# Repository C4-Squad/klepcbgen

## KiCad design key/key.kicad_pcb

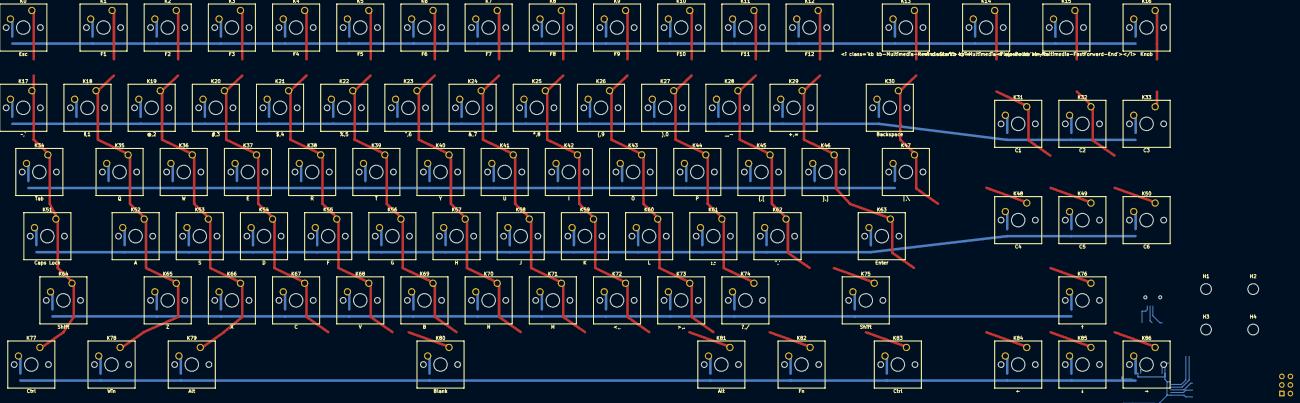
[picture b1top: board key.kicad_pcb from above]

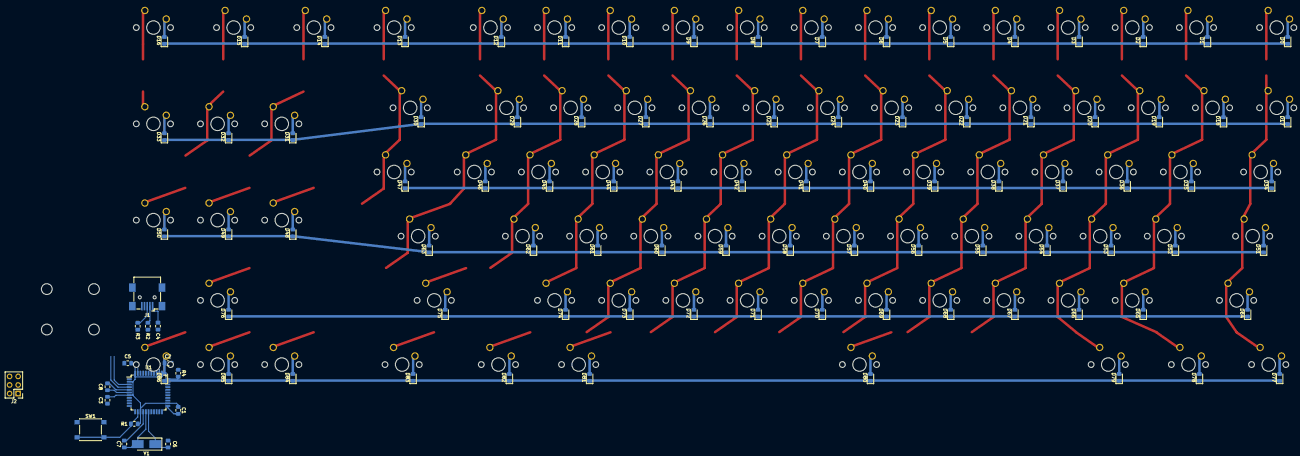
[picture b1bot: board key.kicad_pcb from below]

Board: 2 copper layers, 195 parts (104 on the bottom side), 121 nets.

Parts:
C1, C2, C3, C4: 0.1u; C_0805_2012Metric_Pad1.15x1.40mm_HandSolder
C5: 4.7u; C_0805_2012Metric_Pad1.15x1.40mm_HandSolder
C6, C7: 22p; C_0805_2012Metric_Pad1.15x1.40mm_HandSolder
C8: 1u; C_0805_2012Metric_Pad1.15x1.40mm_HandSolder
D0, D1, D2, D3, D4, D5, D6, D7, D8, D9, D10, D11, D12, D13, D14, D15, D16, D17, D18, D19, D20, D21, D22, D23, D24, D25, D26, D27, D28, D29, D30, D31, D32, D33, D34, D35, D36, D37, D38, D39, D40, D41, D42, D43, D44, D45, D46, D47, D48, D49, D50, D51, D52, D53, D54, D55, D56, D57, D58, D59, D60, D61, D62, D63, D64, D65, D66, D67, D68, D69, D70, D71, D72, D73, D74, D75, D76, D77, D78, D79, D80, D81, D82, D83, D84, D85, D86: D; D_0805_2012Metric_Pad1.15x1.40mm_HandSolder
H1, H2, H3, H4: MountingHole; MountingHole_3.2mm_M3_DIN965
J1: USB_mini_micro_B; USB_Mini-B_Wuerth_65100516121_Horizontal
J2: Conn_02x03_Odd_Even; PinHeader_2x03_P2.54mm_Vertical
K0: Esc; SW_Cherry_MX_1.00u_PCB
K1: F1; SW_Cherry_MX_1.00u_PCB
K2: F2; SW_Cherry_MX_1.00u_PCB
K3: F3; SW_Cherry_MX_1.00u_PCB
K4: F4; SW_Cherry_MX_1.00u_PCB
K5: F5; SW_Cherry_MX_1.00u_PCB
K6: F6; SW_Cherry_MX_1.00u_PCB
K7: F7; SW_Cherry_MX_1.00u_PCB
K8: F8; SW_Cherry_MX_1.00u_PCB
K9: F9; SW_Cherry_MX_1.00u_PCB
K10: F10; SW_Cherry_MX_1.00u_PCB
K11: F11; SW_Cherry_MX_1.00u_PCB
K12: F12; SW_Cherry_MX_1.00u_PCB
K13: <i class='kb kb-Multimedia-Rewind-Start'></i>; SW_Cherry_MX_1.00u_PCB
K14: <i class='kb kb-Multimedia-Play-Pause'></i>; SW_Cherry_MX_1.00u_PCB
K15: <i class='kb kb-Multimedia-FastForward-End'></i>; SW_Cherry_MX_1.00u_PCB
K16: Knob; SW_Cherry_MX_1.00u_PCB
K17: ~~,`; SW_Cherry_MX_1.00u_PCB
K18: !,1; SW_Cherry_MX_1.00u_PCB
K19: @,2; SW_Cherry_MX_1.00u_PCB
K20: #,3; SW_Cherry_MX_1.00u_PCB
K21: $,4; SW_Cherry_MX_1.00u_PCB
K22: %,5; SW_Cherry_MX_1.00u_PCB
K23: ^,6; SW_Cherry_MX_1.00u_PCB
K24: &,7; SW_Cherry_MX_1.00u_PCB
K25: *,8; SW_Cherry_MX_1.00u_PCB
K26: (,9; SW_Cherry_MX_1.00u_PCB
K27: ),0; SW_Cherry_MX_1.00u_PCB
K28: _,-; SW_Cherry_MX_1.00u_PCB
K29: +,=; SW_Cherry_MX_1.00u_PCB
K30: Backspace; SW_Cherry_MX_2.00u_PCB
K31: C1; SW_Cherry_MX_1.00u_PCB
K32: C2; SW_Cherry_MX_1.00u_PCB
K33: C3; SW_Cherry_MX_1.00u_PCB
K34: Tab; SW_Cherry_MX_1.50u_PCB
K35: Q; SW_Cherry_MX_1.00u_PCB
K36: W; SW_Cherry_MX_1.00u_PCB
K37: E; SW_Cherry_MX_1.00u_PCB
K38: R; SW_Cherry_MX_1.00u_PCB
K39: T; SW_Cherry_MX_1.00u_PCB
K40: Y; SW_Cherry_MX_1.00u_PCB
K41: U; SW_Cherry_MX_1.00u_PCB
K42: I; SW_Cherry_MX_1.00u_PCB
K43: O; SW_Cherry_MX_1.00u_PCB
K44: P; SW_Cherry_MX_1.00u_PCB
K45: {,[; SW_Cherry_MX_1.00u_PCB
K46: },]; SW_Cherry_MX_1.00u_PCB
K47: |,\; SW_Cherry_MX_1.50u_PCB
K48: C4; SW_Cherry_MX_1.00u_PCB
K49: C5; SW_Cherry_MX_1.00u_PCB
K50: C6; SW_Cherry_MX_1.00u_PCB
K51: Caps Lock; SW_Cherry_MX_1.75u_PCB
K52: A; SW_Cherry_MX_1.00u_PCB
K53: S; SW_Cherry_MX_1.00u_PCB
K54: D; SW_Cherry_MX_1.00u_PCB
K55: F; SW_Cherry_MX_1.00u_PCB
K56: G; SW_Cherry_MX_1.00u_PCB
K57: H; SW_Cherry_MX_1.00u_PCB
K58: J; SW_Cherry_MX_1.00u_PCB
K59: K; SW_Cherry_MX_1.00u_PCB
K60: L; SW_Cherry_MX_1.00u_PCB
K61: :,;; SW_Cherry_MX_1.00u_PCB
K62: ",'; SW_Cherry_MX_1.00u_PCB
K63: Enter; SW_Cherry_MX_2.25u_PCB
K64: Shift; SW_Cherry_MX_2.25u_PCB
K65: Z; SW_Cherry_MX_1.00u_PCB
K66: X; SW_Cherry_MX_1.00u_PCB
K67: C; SW_Cherry_MX_1.00u_PCB
K68: V; SW_Cherry_MX_1.00u_PCB
K69: B; SW_Cherry_MX_1.00u_PCB
K70: N; SW_Cherry_MX_1.00u_PCB
K71: M; SW_Cherry_MX_1.00u_PCB
K72: <,,; SW_Cherry_MX_1.00u_PCB
K73: >,.; SW_Cherry_MX_1.00u_PCB
K74: ?,/; SW_Cherry_MX_1.00u_PCB
K75: Shift; SW_Cherry_MX_2.75u_PCB
K76: ↑; SW_Cherry_MX_1.00u_PCB
K77: Ctrl; SW_Cherry_MX_1.25u_PCB
K78: Win; SW_Cherry_MX_1.25u_PCB
K79, K81: Alt; SW_Cherry_MX_1.25u_PCB
K80: Blank; SW_Cherry_MX_6.25u_PCB
K82: Fn; SW_Cherry_MX_1.25u_PCB
K83: Ctrl; SW_Cherry_MX_1.75u_PCB
K84: ←; SW_Cherry_MX_1.00u_PCB
K85: ↓; SW_Cherry_MX_1.00u_PCB
K86: →; SW_Cherry_MX_1.00u_PCB
R1, R4: 10k; R_0805_2012Metric_Pad1.15x1.40mm_HandSolder
R2, R3: 22R; R_0805_2012Metric_Pad1.15x1.40mm_HandSolder
SW1: SW_Push; SW_Push_1P1T_NO_6x6mm_H9.5mm
U1: ATmega32U4-AU; TQFP-44_10x10mm_P0.8mm
Y1: Crystal; Crystal_SMD_5032-2Pin_5.0x3.2mm_HandSoldering

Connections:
/Col_0: K0.1, K17.1, K34.1, K51.1, K64.1, K77.1, U1.32
/Col_1: K1.1, K18.1, K35.1, K52.1, K65.1, K78.1, U1.31
/Col_2: K2.1, K19.1, K36.1, K53.1, K66.1, K79.1, U1.30
/Col_3: K3.1, K20.1, K37.1, K54.1, K67.1, K80.1, U1.29
/Col_4: K4.1, K21.1, K38.1, K55.1, K68.1, K81.1, U1.28
/Col_5: K5.1, K22.1, K39.1, K56.1, K69.1, K82.1, U1.27
/Col_6: K6.1, K23.1, K40.1, K57.1, K70.1, K83.1, U1.26
/Col_7: K7.1, K24.1, K41.1, K58.1, K71.1, K84.1, U1.25
/Col_8: K8.1, K25.1, K42.1, K59.1, K72.1, K85.1, U1.36
/Col_9: K9.1, K26.1, K43.1, K60.1, K73.1, K86.1, U1.37
/Col_10: K10.1, K27.1, K44.1, K61.1, K74.1, U1.38
/Col_11: K11.1, K28.1, K45.1, K62.1, K75.1, U1.39
/Col_12: K12.1, K29.1, K46.1, K63.1, K76.1, U1.40
/Col_13: K13.1, K30.1, K47.1, K48.1, U1.41
/Col_14: K14.1, K31.1, K49.1, U1.22
/Col_15: K15.1, K32.1, K50.1, U1.19
/Col_16: K16.1, K33.1, U1.20
/Row_0: D0.1, D1.1, D2.1, D3.1, D4.1, D5.1, D6.1, D7.1, D8.1, D9.1, D10.1, D11.1, D12.1, D13.1, D14.1, D15.1, D16.1, U1.18
/Row_1: D17.1, D18.1, D19.1, D20.1, D21.1, D22.1, D23.1, D24.1, D25.1, D26.1, D27.1, D28.1, D29.1, D30.1, D31.1, D32.1, D33.1, U1.12
/Row_2: D34.1, D35.1, D36.1, D37.1, D38.1, D39.1, D40.1, D41.1, D42.1, D43.1, D44.1, D45.1, D46.1, D47.1, J2.2, U1.11
/Row_3: D48.1, D49.1, D50.1, D51.1, D52.1, D53.1, D54.1, D55.1, D56.1, D57.1, D58.1, D59.1, D60.1, D61.1, D62.1, D63.1, J2.4, U1.10
/Row_4: D64.1, D65.1, D66.1, D67.1, D68.1, D69.1, D70.1, D71.1, D72.1, D73.1, D74.1, D75.1, D76.1, J2.3, U1.9
/Row_5: D77.1, D78.1, D79.1, D80.1, D81.1, D82.1, D83.1, D84.1, D85.1, D86.1, U1.8
GND: C1.2, C2.2, C3.2, C4.2, C5.2, C6.2, C7.2, C8.2, J1.5, J1.6, J2.5, R4.1, SW1.1, U1.5, U1.15, U1.23, U1.35, U1.43
unnamed: C6.1, U1.17, Y1.1
unnamed: C7.1, U1.16, Y1.2
unnamed: C8.1, U1.6
unnamed: D0.2, K0.2
unnamed: D1.2, K1.2
unnamed: D2.2, K2.2
unnamed: D3.2, K3.2
unnamed: D4.2, K4.2
unnamed: D5.2, K5.2
unnamed: D6.2, K6.2
unnamed: D7.2, K7.2
unnamed: D8.2, K8.2
unnamed: D9.2, K9.2
unnamed: D10.2, K10.2
unnamed: D11.2, K11.2
unnamed: D12.2, K12.2
unnamed: D13.2, K13.2
unnamed: D14.2, K14.2
unnamed: D15.2, K15.2
unnamed: D16.2, K16.2
unnamed: D17.2, K17.2
unnamed: D18.2, K18.2
unnamed: D19.2, K19.2
unnamed: D20.2, K20.2
unnamed: D21.2, K21.2
unnamed: D22.2, K22.2
unnamed: D23.2, K23.2
unnamed: D24.2, K24.2
unnamed: D25.2, K25.2
unnamed: D26.2, K26.2
unnamed: D27.2, K27.2
unnamed: D28.2, K28.2
unnamed: D29.2, K29.2
unnamed: D30.2, K30.2
unnamed: D31.2, K31.2
unnamed: D32.2, K32.2
unnamed: D33.2, K33.2
unnamed: D34.2, K34.2
unnamed: D35.2, K35.2
unnamed: D36.2, K36.2
unnamed: D37.2, K37.2
unnamed: D38.2, K38.2
unnamed: D39.2, K39.2
unnamed: D40.2, K40.2
unnamed: D41.2, K41.2
unnamed: D42.2, K42.2
unnamed: D43.2, K43.2
unnamed: D44.2, K44.2
unnamed: D45.2, K45.2
unnamed: D46.2, K46.2
unnamed: D47.2, K47.2
unnamed: D48.2, K48.2
unnamed: D49.2, K49.2
unnamed: D50.2, K50.2
unnamed: D51.2, K51.2
unnamed: D52.2, K52.2
unnamed: D53.2, K53.2
unnamed: D54.2, K54.2
unnamed: D55.2, K55.2
unnamed: D56.2, K56.2
unnamed: D57.2, K57.2
unnamed: D58.2, K58.2
unnamed: D59.2, K59.2
unnamed: D60.2, K60.2
unnamed: D61.2, K61.2
unnamed: D62.2, K62.2
unnamed: D63.2, K63.2
unnamed: D64.2, K64.2
unnamed: D65.2, K65.2
unnamed: D66.2, K66.2
unnamed: D67.2, K67.2
unnamed: D68.2, K68.2
unnamed: D69.2, K69.2
unnamed: D70.2, K70.2
unnamed: D71.2, K71.2
unnamed: D72.2, K72.2
unnamed: D73.2, K73.2
unnamed: D74.2, K74.2
unnamed: D75.2, K75.2
unnamed: D76.2, K76.2
unnamed: D77.2, K77.2
unnamed: D78.2, K78.2
unnamed: D79.2, K79.2
unnamed: D80.2, K80.2
unnamed: D81.2, K81.2
unnamed: D82.2, K82.2
unnamed: D83.2, K83.2
unnamed: D84.2, K84.2
unnamed: D85.2, K85.2
unnamed: D86.2, K86.2
unnamed: J1.2, R2.2
unnamed: J1.3, R3.2
unnamed: R1.1, SW1.2, U1.13
unnamed: R2.1, U1.4
unnamed: R3.1, U1.3
unnamed: R4.2, U1.33
VCC: C1.1, C2.1, C3.1, C4.1, C5.1, J1.1, J2.1, R1.2, U1.2, U1.7, U1.14, U1.24, U1.34, U1.44
